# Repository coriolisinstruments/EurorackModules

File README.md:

# EurorackModules

Open-source eurorack synthesizer modules. All our schematics and pcbs are developed with [KiCad.](http://kicad.org/)

## 1U modules

These are simple (passive) utility modules, designed to fit the Intellijel 1U spec. They are often smaller (6 or 8HP) so you can use them to fill gaps in your system. Except for the Multibus... that one takes up an entire row.

| | Module | Description |
| --- | :----- | :---------- |
|| [LPG](1Utilities/1U_LPG) | A simple passive low-pass gate with -6dB slope in a small 1U package. |
|| [Mute](1Utilities/1U_Mute) | A signal mute (momentary and latching) in a convenient 1U package.|
|| [Mult](1Utilities/1U_Mult) | Dead simple passive multi. Its only feature being very small. |
|| [Multibus](Multibus) | A eurorack module for the distribution of CV signals. |

## Regular (3U) Modules

Just your regular sized eurorack modules.

| | Module | Description |
| --- | :----- | :---------- |
|| [Corona](Corona) | A multi purpose vacuum tube (or valve) drive module with feedback control. |

## Other stuff
| | Thing | Description |
| --- | :----- | :---------- |
|| [PSU Companion](PSUCompanion) | A companion for Bel / Condor / Power One linear power supplies. Goes inbetween the PSU and your busboards. |
|| [Making Vactrols](MakingVactrols) | A little tutorial on making your own vactrols. |

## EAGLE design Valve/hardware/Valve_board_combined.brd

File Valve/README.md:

# Valve
A multi purpose vacuum tube (or valve) drive module with feedback control.

status: work-in-progress

## About
This design is based on Matsumin's well-known "Valvecaster" guitar stompbox design for 12A*7 tubes. This module can act as a regular tube amp with low gain tubes such as the 12AU7. Because the maximum plate voltage is limited to 24V, higher gain tubes are "starved" which introduces distorts the sound in a typical way. The higher the gain, the more pronounced this effect is.

The module consists of 2 boards:
- Tube board that holds (and powers) the actual tube,
- Main board that holds the jacks, pots and the actual drive circuit.

## Tube board
The tube board is connected to the main board via a short (eurorack-standard) 10-pin ribbon cable and incorporates a 6.3V regulator. A jumper on the back of the board allows to select the voltage for the heating filaments. This means the module can also work with the pin-compatible 6N2P (aka 6H2N) Russian model tube, which only differs from the 12A*7 tubes in the voltage needed for earlier mentioned heating filaments (pin 4 and 5).

## Main board
The audio that travels through the circuitry on the main board experiences 5 stages:
- Tube drive,
- Tone filter,
- Adjustable gain (max. +20dB),
- Adjustable Feedback, and
- Dry/Wet mixer.

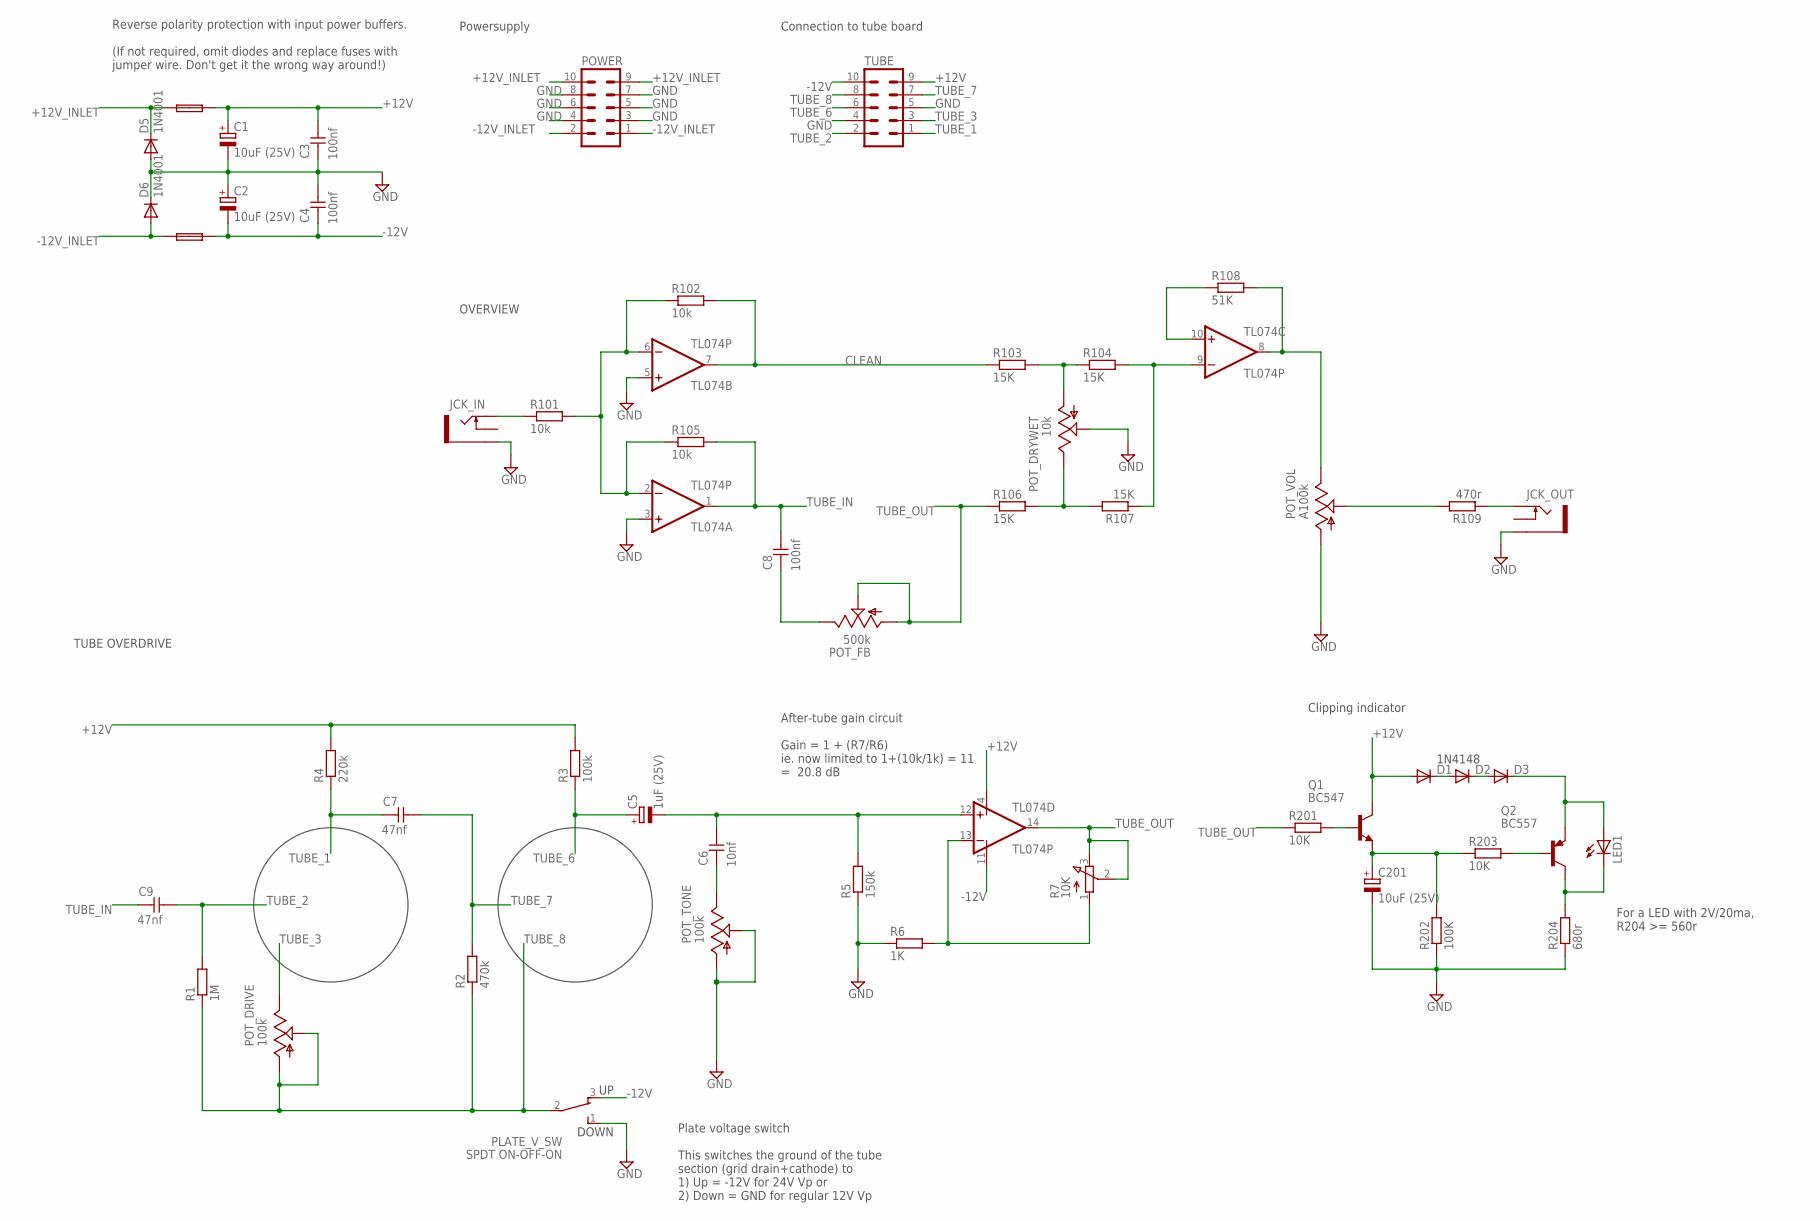
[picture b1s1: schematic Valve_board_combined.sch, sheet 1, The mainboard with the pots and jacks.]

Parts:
C1, C2, C201: 10uF (25V); E2-4
C3, C4, C8: 100nf; C050-024X044
C5: 1uF (25V); E2-4
C6: 10nf; C050-024X044
C7, C9: 47nf; C050-024X044
D1, D2, D3: 1N4148DO35-7; DO35-7
D5, D6: 1N4001; DO41-10
FUSE2: FUSE2; C050H075X075
FUSES: FUSES; C050H075X075
JCK_IN: THONKICONNNEW; WQP-PJ301M-12_JACK
JCK_OUT: THONKICONNNEW; WQP-PJ301M-12_JACK
LED1: LED3MM
PLATE_V_SW: SPDT ON-OFF-ON; SPDT-VERTICAL-TOP-SUBMINI-MULTICOMP
POT_DRIVE: 100k; EVUF
POT_DRYWET: 10k; EVUF
POT_FB: 500k; EVUF
POT_TONE: 100k; EVUF
POT_VOL: A100k; EVUF
POWER: MA05-2
Q1: BC547; TO92
Q2: BC557; TO92-EBC
R1: 1M; 0207/7
R2: 470k; 0207/7
R3: 100k; 0207/7
R4: 220k; 0207/7
R5: 150k; 0207/7
R6: 1K; 0207/7
R7: 10K; EVUF
R101, R102, R105: 10k; 0207/7
R103, R104, R106, R107: 15K; 0207/7
R108: 51K; 0207/7
R109: 470r; 0207/7
R201, R203: 10K; 0207/7
R202: 100K; 0207/7
R204: 680r; 0207/7
TL074: TL074P; DIL14
TUBE: MA05-2

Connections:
+12V: C1.+, C3.1, D1.A, FUSES.2, Q1.3 (C), R3.2, R4.2, TL074.4 (V+), TUBE.9
+12V_INLET: D5.C, FUSES.1, POWER.9, POWER.10
-12V: C2.-, C4.2, FUSE2.2, PLATE_V_SW.3, TL074.11 (V-), TUBE.10
-12V_INLET: D6.A, FUSE2.1, POWER.1, POWER.2
CLEAN: R102.2, R103.1, TL074.7 (OUT)
GND: C1.-, C2.+, C3.2, C4.1, C201.-, D5.A, D6.C, JCK_IN.P$3_SLEEVE (SLEEVE), JCK_OUT.P$3_SLEEVE (SLEEVE), PLATE_V_SW.1, POT_DRYWET.2 (S), POT_TONE.1 (A), POT_TONE.2 (S), POT_VOL.1 (A), POWER.3, POWER.4, POWER.5, POWER.6, POWER.7, POWER.8, R5.1, R6.1, R202.1, R204.1, TL074.3 (+IN), TL074.5 (+IN), TUBE.4, TUBE.5
unnamed: JCK_IN.P$1_TIP (TIP), R101.1
unnamed: JCK_OUT.P$1_TIP (TIP), R109.1
unnamed: R6.2, R7.1 (A), TL074.13 (-IN)
unnamed: C6.2, POT_TONE.3 (E)
unnamed: POT_VOL.2 (S), R109.2
unnamed: POT_DRYWET.1 (A), R103.2, R104.1
unnamed: C8.2, POT_FB.3 (E)
unnamed: R101.2, R102.1, R105.1, TL074.2 (-IN), TL074.6 (-IN)
unnamed: POT_DRYWET.3 (E), R106.2, R107.2
unnamed: Q1.2 (B), R201.2
unnamed: R104.2, R107.1, TL074.9 (-IN)
unnamed: R108.1, TL074.10 (+IN)
unnamed: POT_VOL.3 (E), R108.2, TL074.8 (OUT)
unnamed: C201.+, Q1.1 (E), R202.2, R203.1
unnamed: D1.C, D2.A
unnamed: D2.C, D3.A
unnamed: D3.C, LED1.A, Q2.E
unnamed: LED1.K (C), Q2.C, R204.2
unnamed: Q2.B, R203.2
TUBE_1: C7.2, R4.1, TUBE.1
TUBE_2: C9.1, R1.2, TUBE.2
TUBE_3: POT_DRIVE.3 (E), TUBE.3
TUBE_6: C5.+, R3.1, TUBE.6
TUBE_7: C7.1, R2.2, TUBE.7
TUBE_8: PLATE_V_SW.2, POT_DRIVE.1 (A), POT_DRIVE.2 (S), R1.1, R2.1, TUBE.8
TUBE_IN: C8.1, C9.2, R105.2, TL074.1 (OUT)
TUBE_OUT: POT_FB.1 (A), POT_FB.2 (S), R7.2 (S), R7.3 (E), R106.1, R201.1, TL074.14 (OUT)
VOL_3: C5.-, C6.1, R5.2, TL074.12 (+IN)

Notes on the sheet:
Reverse polarity protection with input power buffers. (If not required, omit diodes and replace fuses with jumper wire. Don't get it the wrong way around!)
Powersupply
Connection to tube board
OVERVIEW
After-tube gain circuit Gain = 1 + (R7/R6) ie. now limited to 1+(10k/1k) = 11 = 20.8 dB
TUBE OVERDRIVE
1N4148
Clipping indicator
For a LED with 2V/20ma, R204 >= 560r
Plate voltage switch This switches the ground of the tube section (grid drain+cathode) to 1) Up = -12V for 24V Vp or 2) Down = GND for regular 12V Vp

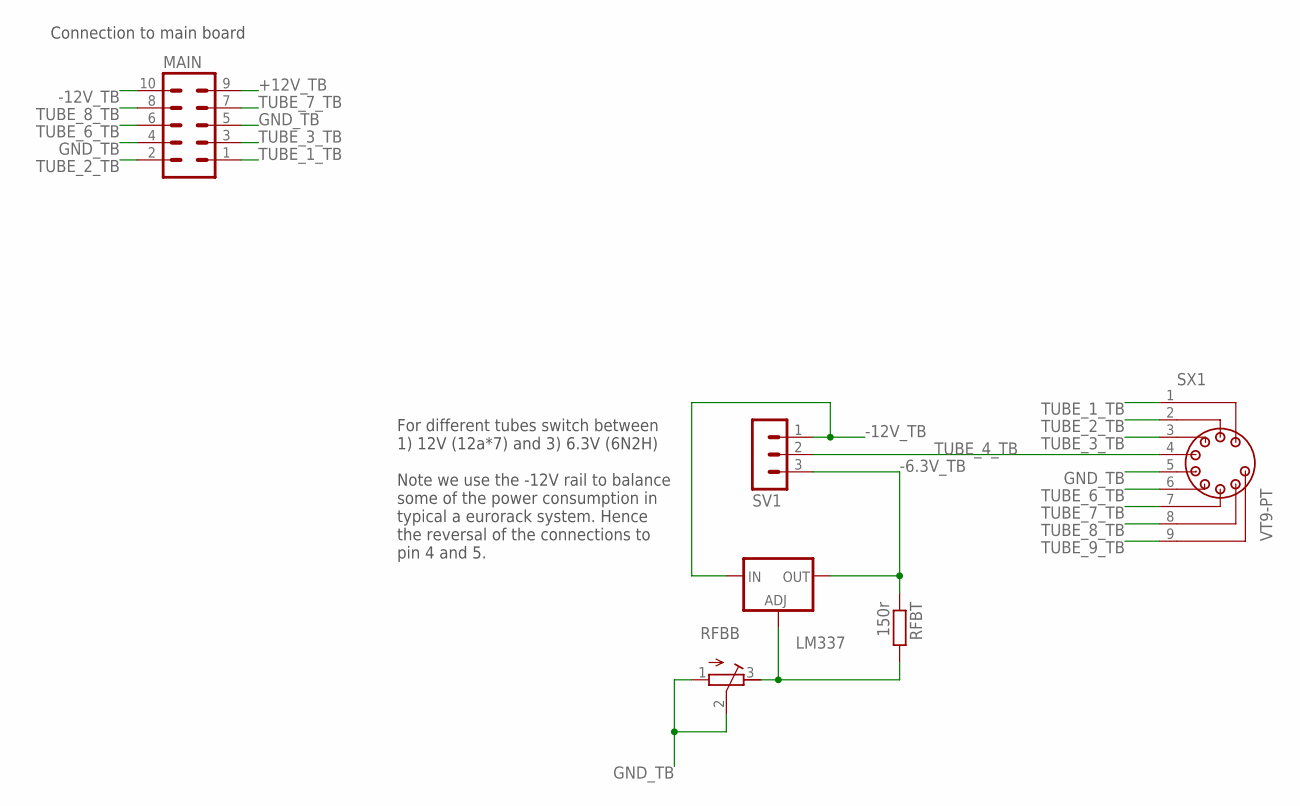
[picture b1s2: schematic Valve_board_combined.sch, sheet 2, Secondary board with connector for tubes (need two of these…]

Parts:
LM337: LM337TS; 337TS
MAIN: MA05-2
RFBB: R-TRIMM3296W; RTRIM3296W
RFBT: 150r; 0207/7
SV1: MA03-1
SX1: VT9-PT

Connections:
+12V_TB: MAIN.9
-6.3V_TB: LM337.3 (OUT), RFBT.1, SV1.3
-12V_TB: LM337.2 (IN), MAIN.10, SV1.1
GND_TB: MAIN.4, MAIN.5, RFBB.1 (A), RFBB.2 (S), SX1.5
unnamed: LM337.1 (ADJ), RFBB.3 (E), RFBT.2
TUBE_1_TB: MAIN.1, SX1.1
TUBE_2_TB: MAIN.2, SX1.2
TUBE_3_TB: MAIN.3, SX1.3
TUBE_4_TB: SV1.2, SX1.4
TUBE_6_TB: MAIN.6, SX1.6
TUBE_7_TB: MAIN.7, SX1.7
TUBE_8_TB: MAIN.8, SX1.8
TUBE_9_TB: SX1.9

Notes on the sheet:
Connection to main board
For different tubes switch between 1) 12V (12a*7) and 3) 6.3V (6N2H) Note we use the -12V rail to balance some of the power consumption in typical a eurorack system. Hence the reversal of the connections to pin 4 and 5.

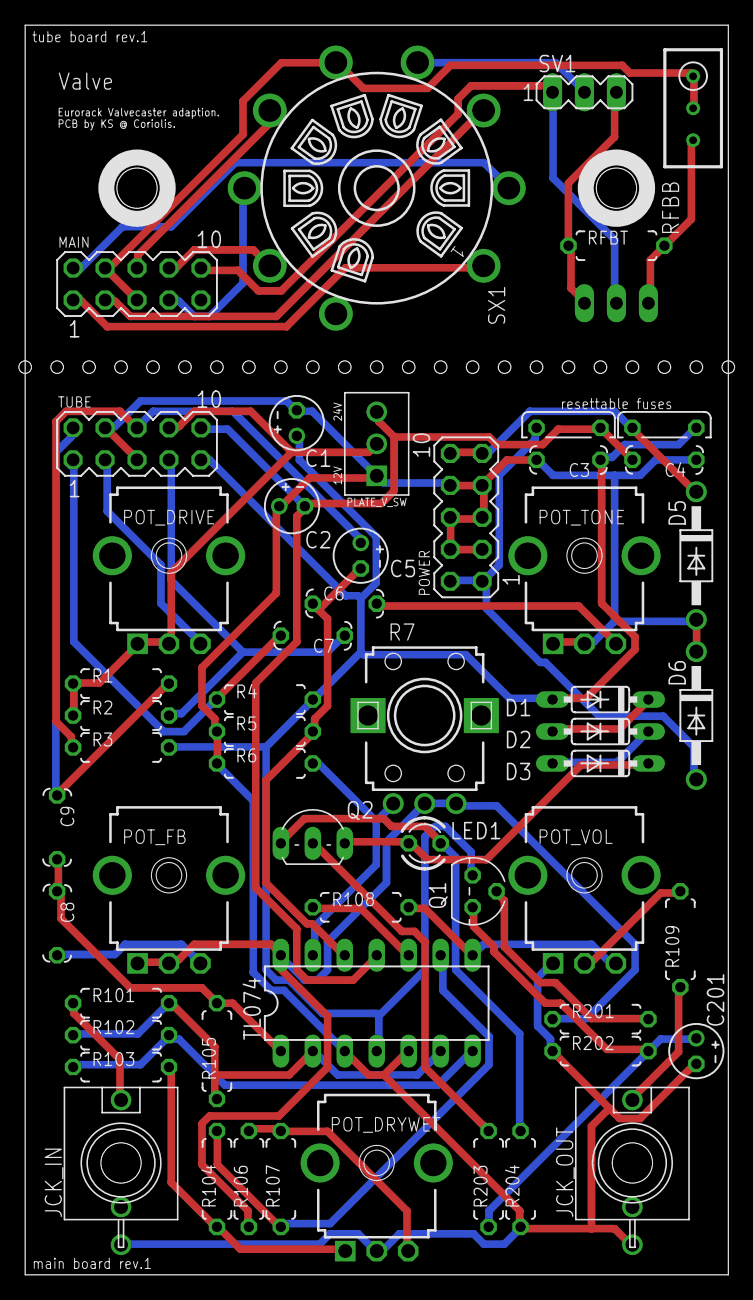
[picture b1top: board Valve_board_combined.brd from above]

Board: 2 copper layers, 55.9 x 99.3 mm, 57 parts (1 on the bottom side), 45 nets.

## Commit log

2018-01-12 Transfer of local version
    Eagle files and panel svg
2018-01-12 Added readme and new logo to panel.
2018-01-13 New project files
    Also contains templates (for power and often used components).
2018-01-13 Finished front board for channel 1.
2018-01-14 After weekend commit.
    Working on 8hp solution for single channel. Need to align pins and boards.
2018-01-19 Temp commit.
2018-01-20 Finished up track routing.
2018-01-21 Finishing up the boards
2018-01-21 Ignoring pcb-bak files
2018-01-27 Added readme and clean up files
2018-01-29 More LFO stuff
    Added panel; restructured some folders.
2018-01-30 Transition to KiCad, added panel
2018-01-30 Reordering folders, renaming of modules, addition of Aphelion
2018-01-30 Updated readme for Aphelion
2018-01-30 Updated front panel express file
2018-01-30 Updated eurorack psu template
2018-02-03 Redesigned Aphelion PCBs and panel to 8hp
2018-02-04 Changed Aphelion panel to use knobs instead of trimpots
2018-02-11 Reworked schematic after breadboarding
2018-02-12 Updated pcb and panel
2018-02-24 Updated CV for feedback
2018-03-04 Change to 16hp; optimizing board after breadboarding
2018-03-26 Clean up panel directory. Added CV inputs.
2018-04-04 Minor mods to panel. Added H11F1 to schematic for drive cv.
2018-08-11 Added TWObyTWO Tone files. Updated Corona graphics.
    A new module! A quad Low-Pass Gate (LPG) with some normalization. Completely passive and only a few components. Based on the Two Tone module by Ben Moren.
2018-08-11 Updated readme's.
    Updated readme's.
2018-08-11 Small revision to TWObyTWO panel design
2018-08-12 Small board and panel changes.
2018-08-18 Two new 1U modules. Updated gerbers too.
    Added the first iteration of the Mute and LPG 1U modules.
2018-08-19 Updated 1U_Mute panel. Updated readme's.
2018-08-19 Updated readme's.
2018-08-19 Updated .gitignore
2018-08-19 Added breadboard image for 1U_LPG.
2018-08-20 Modified LPG pcb and schematic with non-polarized cap. Removed old .drl file. Updated readme.
2018-08-26 Redesigned LPG to be 2-pole. Added Vactrol making tutorial.
2018-08-26 Updated readme for LPG
2018-08-26 Updated readme.
2018-08-26 Updated readmes.
2018-08-26 Updated readme and resized images.
2018-08-26 Updated gerbers of 1U modules.
2018-08-27 Moved 1Utilities series. Added 1U passive mult stuff.
2018-08-28 Updated 1U Mute and Mult.
    Panel art, gerbers, pcb for Mult. Removed useless LED section from Mute (because passive).
2018-08-29 Updated panel art and gerbers.
2018-08-29 Revision 2 of LPG. Updated Mult graphics.
    Rotated tone potentiometer to allow greater diversity (tall trimmer pots, t18, shaft etc.)
2018-08-29 More 1U panel art updates. Fancy!
2018-08-30 Updated 1U art for LPG and Mute. Removed TwoByTwo tone module (replaced by 1U LPG)
2018-08-30 Readme changes
2018-08-30 Readme changes.
2018-08-31 Updated readme with pictures of modules.
2018-08-31 Small gfx update (slightly less beefy).
2018-11-07 Added PSU Companion thing
    And editted the readme.
2018-11-08 Added board render to readme
2018-11-09 Updated Q1 to 2N3904. Adjusted component values.
    After breadboarding, adjust component values that work well in practice. Current design delays start up about .5s (ballpark figure).
2018-11-11 Redoing board layout.
    (WIP) Enlarged main board for better placement of components. Simplified illumination of tube.
2018-11-12 Added pins for optional external power for tube heaters.
2018-11-12 Revised board layout. Added panel.
2018-11-12 Added PCB panel. Added renders of boards.
2018-11-13 Added simple led driver to tube board.
2018-11-13 Added Coriolis Logo to tube board
2018-11-14 Slightly revised board layout.
    Better spacing of the bottom pots.
2018-11-15 Updated Corona panel art (and panel).
2018-11-16 Routed mainboard. Refactored components to new KiCad standard. Added board renders.
2018-11-17 Corona: Reworked layout main board. Reworked panel.
2018-11-17 Updated art pdfs.
2018-11-19 Corona: add 1V offset to vactrols. Fixed alignment issue with tube board.
2018-11-19 Corona: new gerbers. Fixed panelboard layout.
    TODO: update graphics.
2018-11-19 Corona: fixed panel art alignment issues. Reorganized folders.
2018-11-20 Corono: revised board renders.
2018-11-27 Corona: added BOM.
2018-12-08 Corona: updated panel art. Improved auto indicator under tube.
2018-12-09 Corona: revised tubeboard layout. Updated gerbers.
2019-01-05 New module: 1U cv bus (104hp)
    First commit (art needs a once over though)
2019-01-09 Fixed drc in schematic added front and main boards
2019-01-10 Finished layout for boards.
    TODO: revise art/LED layout
2019-01-11 Finished routing of front and main boards.
2019-01-12 Finished new layout of panel and front board.
    Needed to revise layout because routing became impossible.
2019-01-13 Added gain potentiometers. Revised hardware.
2019-01-14 Fixed accidental swap between panel art pdfs.
2019-02-08 Removed undeveloped module designs
2019-02-12 Added new Multibus cv distribution module
2019-02-12 Updated readme's
2019-03-10 New project: the SnackBus PSU
2019-03-31 First steps to splitting in control and main board.
2019-04-01 More moving of parts.
2019-04-01 Transition to 0805 resistors for main board.
    Need the space....
2019-04-01 More shifting around components
2019-04-02 More refactoring and opamps to SMD
2019-04-03 Added panel. Removed cv for tone. Fixed error in plate voltage switch.
    Todo: routing mainboard, routing tubeboard(?), re-export gerbers, finish art.
2019-04-04 Updated control board layout. Updated gerber packages.
2019-04-06 Finished up pcbs and first iteration of panel art.
2021-11-08 Update README.md
    https://forum.kicad.info/t/warning-avoid-all-links-to-kicad-pcb-org-use-kicad-org/31521
